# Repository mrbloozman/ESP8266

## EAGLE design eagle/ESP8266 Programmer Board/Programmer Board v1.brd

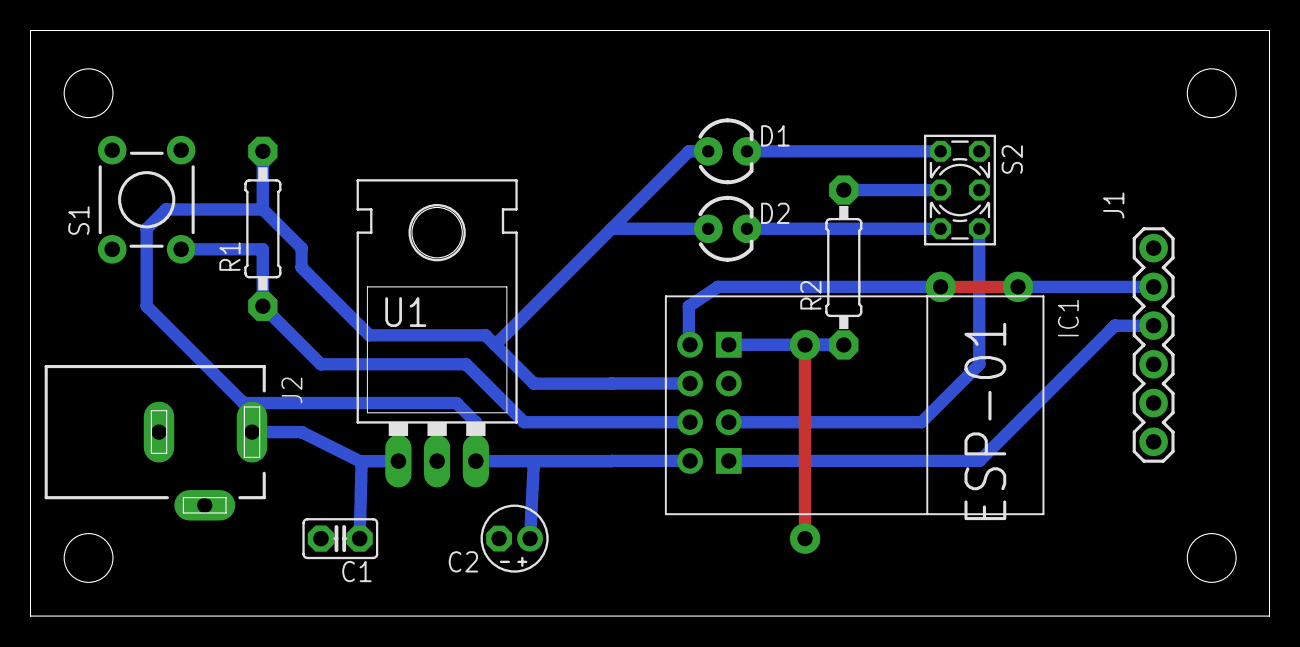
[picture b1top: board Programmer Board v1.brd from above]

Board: 2 copper layers, 81.3 x 38.4 mm, 12 parts (0 on the bottom side), 10 nets.

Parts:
C1: 0.1uF; C025-025X050
C2: 10uF; E2-4
D1: RUN; LED3MM
D2: PROG; LED3MM
IC1: ESP01
J1: FTDI; FTDI_BASIC
J2: DCJ0202
R1: 10k; 0207/10
R2: 75; 0207/10
S1: RESET; TACTILE-PTH
S2: 9450-2
U1: LM7833; TO-220-ALT

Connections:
+3V3: C2.+, D1.A, D2.A, IC1.CH_PD, IC1.VCC, R1.2, U1.OUT
GND: C1.2, C2.-, IC1.GND, J1.GND, J2.3, R2.1, S1.1, S2.5, U1.GND
GPIO0: IC1.GPIO0, S2.6
unnamed: D2.K, S2.3
unnamed: R2.2, S2.2
unnamed: D1.K, S2.1
RST: IC1.RST, R1.1, S1.3
RX: IC1.RX, J1.TXO
TX: IC1.TX, J1.RXI
VCC: C1.1, J2.1, U1.IN

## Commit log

2017-05-14 Updating switches
2017-05-15 Board routing
2017-05-16 Adding Arduino dir
2017-05-16 Relay Board
2017-05-17 Relay Board layout
2017-06-16 Power Supply regulator ref design
2017-06-17 Low Voltage Regular schematics

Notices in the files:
parts and their libraries:
SparkFun-Connectors: Licensing: Creative Commons ShareAlike 4.0 International - https://creativecommons.org/licenses/by-sa/4.0
